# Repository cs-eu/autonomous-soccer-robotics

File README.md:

# Autonomous Soccer Robot

An autonomous, competition-ready soccer robot designed and built for a educational robotics competition.

---

## Overview

The **Autonomous Soccer Robot** was engineered to:

* Detect and track a ball using 360° vision
* Navigate the field holonomically in any direction
* Handle and shoot the ball autonomously
* Operate completely untethered under RoboCupJunior Soccer rules

Every part — from the **mechanical design** and **custom PCBs** to the **embedded firmware** and **computer vision** algorithms — was developed by our team.

This repository provides a complete, open-source reference for educational and research use.

---

## Project Structure

```
.
├── docs/                # Documentation and reference material
│   ├── electronics/     # Schematics, PCB layouts, and Eagle files
│   ├── hardware/        # CAD designs, drawings, and mechanical notes
│   └── parts-lists/     # Component, ordering, and assembly lists
│
├── firmware/            # Embedded control software (C/C++ / PlatformIO)
│   ├── calibration-tools/  # Sensor calibration and testing utilities
│   ├── main-controller/    # High-level control (movement, PID, logic)
│   ├── sensor-node/        # Sensor acquisition and preprocessing
│   └── tests/              # Unit and integration tests
│
├── libraries/           # Shared hardware abstraction and logic libraries
│   ├── Bodensensoren/   # Floor sensor modules
│   ├── IMU/             # IMU driver and orientation estimation
│   ├── TOF/             # Time-of-Flight distance sensing
│   ├── Motors/          # Motor control and PID regulation
│   ├── TACTICS/         # Robot state machine and strategy modules
│   └── ...              # Additional hardware interface libraries
│
├── mechanical/          # Physical design and fabrication files
│   ├── 3d-models/       # Fusion 360 models and 3D-print files (.stl, .f3d)
│   ├── eagle-pcb/       # Custom PCB layouts and Eagle libraries
│   └── metal-fabrication/ # CNC drawings, step files, and laser-cut designs
│
└── vision/              # Computer vision and image processing
    ├── docker/          # Dockerfiles for OpenCV build environments
    └── tinkerboard/     # Tinker Board vision software (Python + OpenCV)
```

---

## System Architecture

### Hardware Overview

* **Drive System:** Three-wheel omnidirectional base (holonomic drive)
* **Dribbler:** DC-motor-driven adhesive roller for ball handling
* **Kicker:** Solenoid-based shooting mechanism powered via capacitor buffer
* **Main Controller:** Dual **Teensy 3.6** microcontrollers for control & sensing
* **Vision Processor:** **ASUS Tinker Board** running OpenCV (Python)
* **Sensors:**

  * Raspberry Pi camera + parabolic mirror (360° vision)
  * 4× Time-of-Flight (ToF) distance sensors
  * 32× photoresistor array with RGB illumination for boundary detection

---

## Software Overview

| Layer             | Platform                     | Language                  | Description                                           |
| ----------------- | ---------------------------- | ------------------------- | ----------------------------------------------------- |
| **Vision**        | Tinker Board (SBC)           | Python + OpenCV           | Detects the ball and extracts angular bearing         |
| **Control**       | Teensy 3.6                   | C/C++ (Arduino Framework) | Motion control, PID regulation, actuator management   |
| **Communication** | Serial protocol (custom CRC) | C/Python                  | Reliable low-latency data exchange (<20 ms loop time) |

### Control Loop

The control system computes translational and rotational velocities from sensor inputs, applying:
[
u(t) = K_p e(t) + K_i \int e(t),dt + K_d \frac{de(t)}{dt}
]
Each wheel’s speed is regulated through independent PID loops for smooth, responsive motion.

---

## Mechanical Design

The chassis combines **CNC-milled aluminum** for structural integrity with **3D-printed polymer shells** for lightweight coverage and modular maintenance.
All components were modeled in **Autodesk Fusion 360**, allowing precise alignment and rapid iteration.

---

## Electronics

* **Custom PCBs** for motor drivers, solenoid control, and power regulation
* Designed using **Autodesk Eagle**
* Multiple voltage rails (12V / 5V / 3.3V) with overcurrent and thermal protection
* Modular connectors for fast servicing during competition

---

## Vision and Perception

The 360° vision system uses a **catadioptric setup** (camera + parabolic mirror) to obtain a full panoramic field view.
Processing steps include:

1. Image unwarping to cylindrical projection
2. Color filtering to detect the orange ball
3. Contour and centroid extraction
4. Angular position estimation relative to robot center

Additional data from ToF sensors and photoresistors provide:

* Boundary line detection
* Obstacle proximity sensing
* Position estimation support

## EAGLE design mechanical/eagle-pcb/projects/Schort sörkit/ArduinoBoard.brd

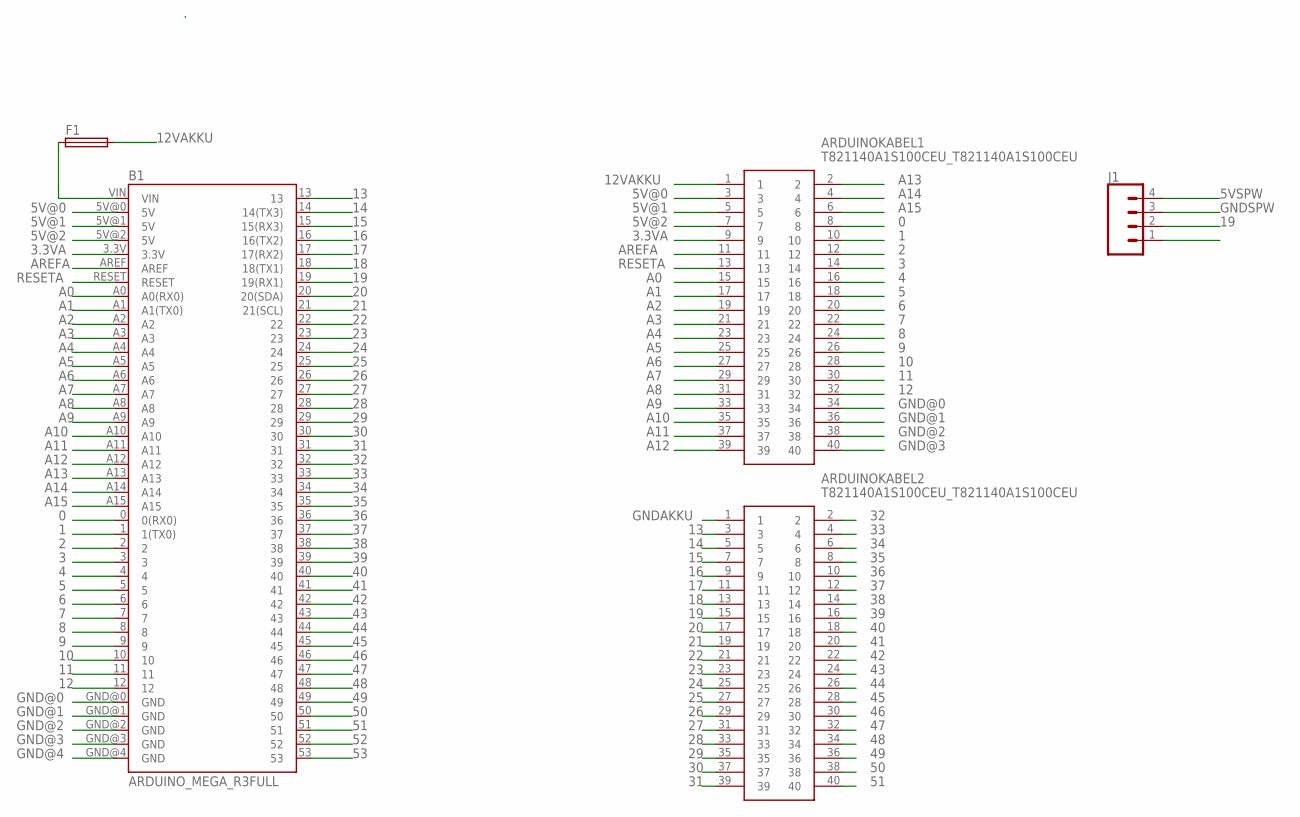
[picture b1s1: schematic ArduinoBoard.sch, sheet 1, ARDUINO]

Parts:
ARDUINOKABEL1, ARDUINOKABEL2: T821140A1S100CEU_T821140A1S100CEU; T821140A1S100CEU_SHDR40W64P254X254_2X20_5842X89
B1: ARDUINO_MEGA_R3FULL; ARDUINO_MEGA
F1: SH25
J1: CONN_04; 1X04

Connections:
0: ARDUINOKABEL1.8, B1.0 (0(RX0))
1: ARDUINOKABEL1.10, B1.1 (1(TX0))
2: ARDUINOKABEL1.12, B1.2; also elsewhere on the board
3: ARDUINOKABEL1.14, B1.3; also elsewhere on the board
3.3VA: ARDUINOKABEL1.9, B1.3.3V
4: ARDUINOKABEL1.16, B1.4; also elsewhere on the board
5: ARDUINOKABEL1.18, B1.5; also elsewhere on the board
5V@0: ARDUINOKABEL1.3, B1.5V@0 (5V); also elsewhere on the board
5V@1: ARDUINOKABEL1.5, B1.5V@1 (5V)
5V@2: ARDUINOKABEL1.7, B1.5V@2 (5V)
6: ARDUINOKABEL1.20, B1.6; also elsewhere on the board
7: ARDUINOKABEL1.22, B1.7
8: ARDUINOKABEL1.24, B1.8; also elsewhere on the board
9: ARDUINOKABEL1.26, B1.9
10: ARDUINOKABEL1.28, B1.10
11: ARDUINOKABEL1.30, B1.11
12: ARDUINOKABEL1.32, B1.12
12VAKKU: ARDUINOKABEL1.1, F1.2
13: ARDUINOKABEL2.3, B1.13
14: ARDUINOKABEL2.5, B1.14 (14(TX3))
15: ARDUINOKABEL2.7, B1.15 (15(RX3))
16: ARDUINOKABEL2.9, B1.16 (16(TX2))
17: ARDUINOKABEL2.11, B1.17 (17(RX2))
18: ARDUINOKABEL2.13, B1.18 (18(TX1)); also elsewhere on the board
19: ARDUINOKABEL2.15, B1.19 (19(RX1)), J1.2; also elsewhere on the board
20: ARDUINOKABEL2.17, B1.20 (20(SDA))
21: ARDUINOKABEL2.19, B1.21 (21(SCL))
22: ARDUINOKABEL2.21, B1.22
23: ARDUINOKABEL2.23, B1.23
24: ARDUINOKABEL2.25, B1.24
25: ARDUINOKABEL2.27, B1.25
26: ARDUINOKABEL2.29, B1.26
27: ARDUINOKABEL2.31, B1.27
28: ARDUINOKABEL2.33, B1.28
29: ARDUINOKABEL2.35, B1.29
30: ARDUINOKABEL2.37, B1.30
31: ARDUINOKABEL2.39, B1.31
32: ARDUINOKABEL2.2, B1.32
33: ARDUINOKABEL2.4, B1.33
34: ARDUINOKABEL2.6, B1.34
35: ARDUINOKABEL2.8, B1.35
36: ARDUINOKABEL2.10, B1.36
37: ARDUINOKABEL2.12, B1.37
38: ARDUINOKABEL2.14, B1.38
39: ARDUINOKABEL2.16, B1.39
40: ARDUINOKABEL2.18, B1.40
41: ARDUINOKABEL2.20, B1.41
42: ARDUINOKABEL2.22, B1.42
43: ARDUINOKABEL2.24, B1.43
44: ARDUINOKABEL2.26, B1.44
45: ARDUINOKABEL2.28, B1.45
46: ARDUINOKABEL2.30, B1.46
47: ARDUINOKABEL2.32, B1.47
48: ARDUINOKABEL2.34, B1.48
49: ARDUINOKABEL2.36, B1.49
50: ARDUINOKABEL2.38, B1.50
51: ARDUINOKABEL2.40, B1.51
52: B1.52
53: B1.53
A0: ARDUINOKABEL1.15, B1.A0 (A0(RX0))
A1: ARDUINOKABEL1.17, B1.A1 (A1(TX0))
A2: ARDUINOKABEL1.19, B1.A2
A3: ARDUINOKABEL1.21, B1.A3
A4: ARDUINOKABEL1.23, B1.A4
A5: ARDUINOKABEL1.25, B1.A5
A6: ARDUINOKABEL1.27, B1.A6
A7: ARDUINOKABEL1.29, B1.A7
A8: ARDUINOKABEL1.31, B1.A8
A9: ARDUINOKABEL1.33, B1.A9
A10: ARDUINOKABEL1.35, B1.A10
A11: ARDUINOKABEL1.37, B1.A11
A12: ARDUINOKABEL1.39, B1.A12
A13: ARDUINOKABEL1.2, B1.A13
A14: ARDUINOKABEL1.4, B1.A14
A15: ARDUINOKABEL1.6, B1.A15
AREFA: ARDUINOKABEL1.11, B1.AREF
GND@0: ARDUINOKABEL1.34, B1.GND@0 (GND); also elsewhere on the board
GND@1: ARDUINOKABEL1.36, B1.GND@1 (GND)
GND@2: ARDUINOKABEL1.38, B1.GND@2 (GND)
GND@3: ARDUINOKABEL1.40, B1.GND@3 (GND)
GND@4: B1.GND@4 (GND)
GNDAKKU: ARDUINOKABEL2.1
RESETA: ARDUINOKABEL1.13, B1.RESET
VIN: B1.VIN, F1.1

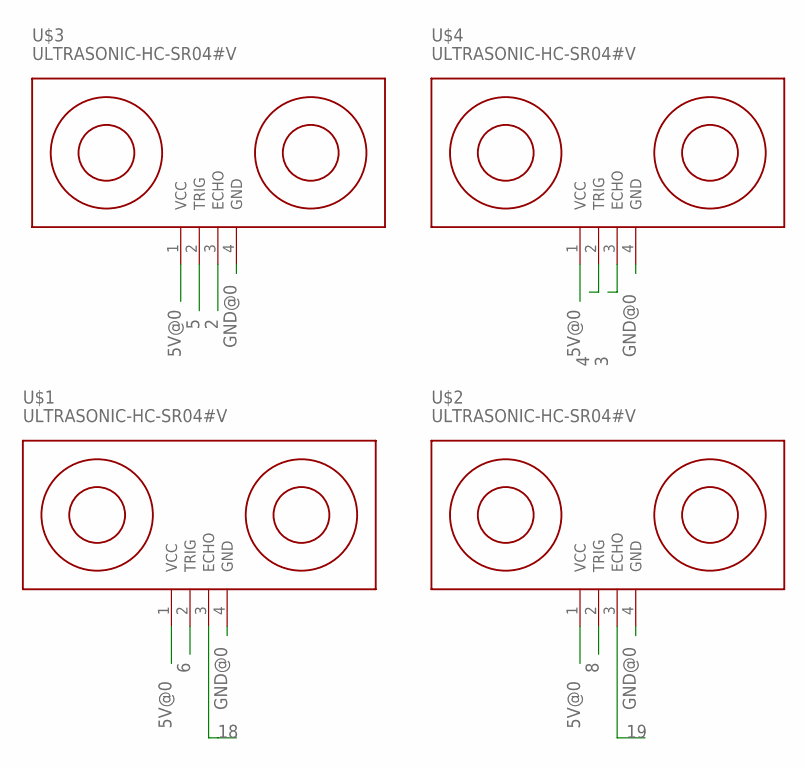
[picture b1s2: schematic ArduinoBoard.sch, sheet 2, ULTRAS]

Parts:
U$1, U$2, U$3, U$4: ULTRASONIC-HC-SR04#V

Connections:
2: U$3.3 (ECHO); also elsewhere on the board
3: U$4.3 (ECHO); also elsewhere on the board
4: U$4.2 (TRIG); also elsewhere on the board
5: U$3.2 (TRIG); also elsewhere on the board
5V@0: U$1.1 (VCC), U$2.1 (VCC), U$3.1 (VCC), U$4.1 (VCC); also elsewhere on the board
6: U$1.2 (TRIG); also elsewhere on the board
8: U$2.2 (TRIG); also elsewhere on the board
18: U$1.3 (ECHO); also elsewhere on the board
19: U$2.3 (ECHO); also elsewhere on the board
GND@0: U$1.4 (GND), U$2.4 (GND), U$3.4 (GND), U$4.4 (GND); also elsewhere on the board

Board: 2 copper layers, 9 parts (0 on the bottom side), 80 nets, no tracks yet.

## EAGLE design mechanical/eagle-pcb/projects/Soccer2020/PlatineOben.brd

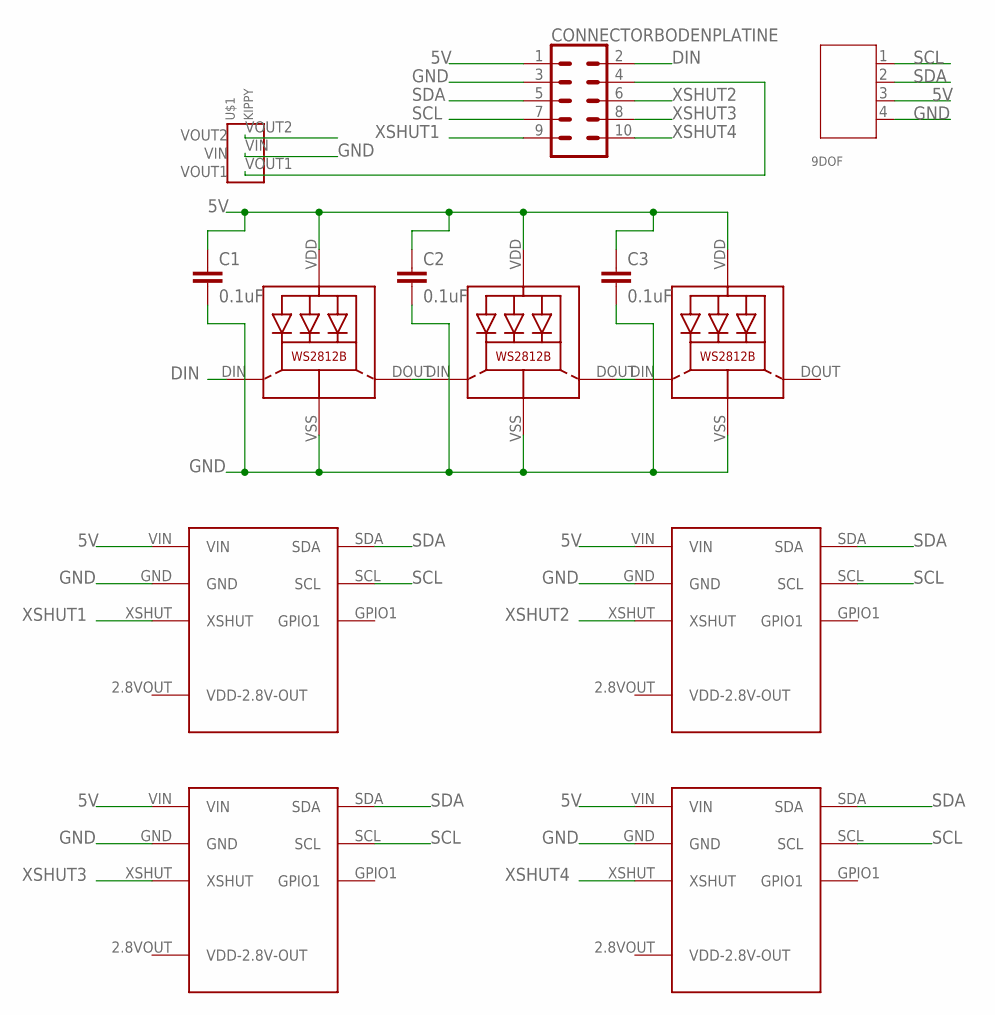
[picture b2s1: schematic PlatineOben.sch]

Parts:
9DOF: 4P-2.0; JST-PH4
C1, C2, C3: 0.1uF; C0805
CONNECTORBODENPLATINE: CONN_05X2; 2X5-SHROUDED(3D)
LED1, LED2, LED3: WS2812B
TOFH: TOFPOLOLUSTEHEND; TOFPOLOLU_STEHEND
TOFL: TOFPOLOLUSTEHEND; TOFPOLOLU_STEHEND
TOFR: TOFPOLOLUSTEHEND; TOFPOLOLU_STEHEND
TOFV: TOFPOLOLUSTEHEND; TOFPOLOLU_STEHEND
U$1: KIPPY

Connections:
5V: 9DOF.3, C1.1, C2.1, C3.1, CONNECTORBODENPLATINE.1, LED1.VDD, LED2.VDD, LED3.VDD, TOFH.VIN, TOFL.VIN, TOFR.VIN, TOFV.VIN
DIN: CONNECTORBODENPLATINE.2, LED1.DIN (DI)
GND: 9DOF.4, C1.2, C2.2, C3.2, CONNECTORBODENPLATINE.3, LED1.VSS (GND), LED2.VSS (GND), LED3.VSS (GND), TOFH.GND, TOFL.GND, TOFR.GND, TOFV.GND, U$1.VIN
unnamed: CONNECTORBODENPLATINE.4, U$1.VOUT1
unnamed: LED1.DOUT (DO), LED2.DIN (DI)
unnamed: LED2.DOUT (DO), LED3.DIN (DI)
SCL: 9DOF.1, CONNECTORBODENPLATINE.7, TOFH.SCL, TOFL.SCL, TOFR.SCL, TOFV.SCL
SDA: 9DOF.2, CONNECTORBODENPLATINE.5, TOFH.SDA, TOFL.SDA, TOFR.SDA, TOFV.SDA
XSHUT1: CONNECTORBODENPLATINE.9, TOFR.XSHUT
XSHUT2: CONNECTORBODENPLATINE.6, TOFL.XSHUT
XSHUT3: CONNECTORBODENPLATINE.8, TOFV.XSHUT
XSHUT4: CONNECTORBODENPLATINE.10, TOFH.XSHUT

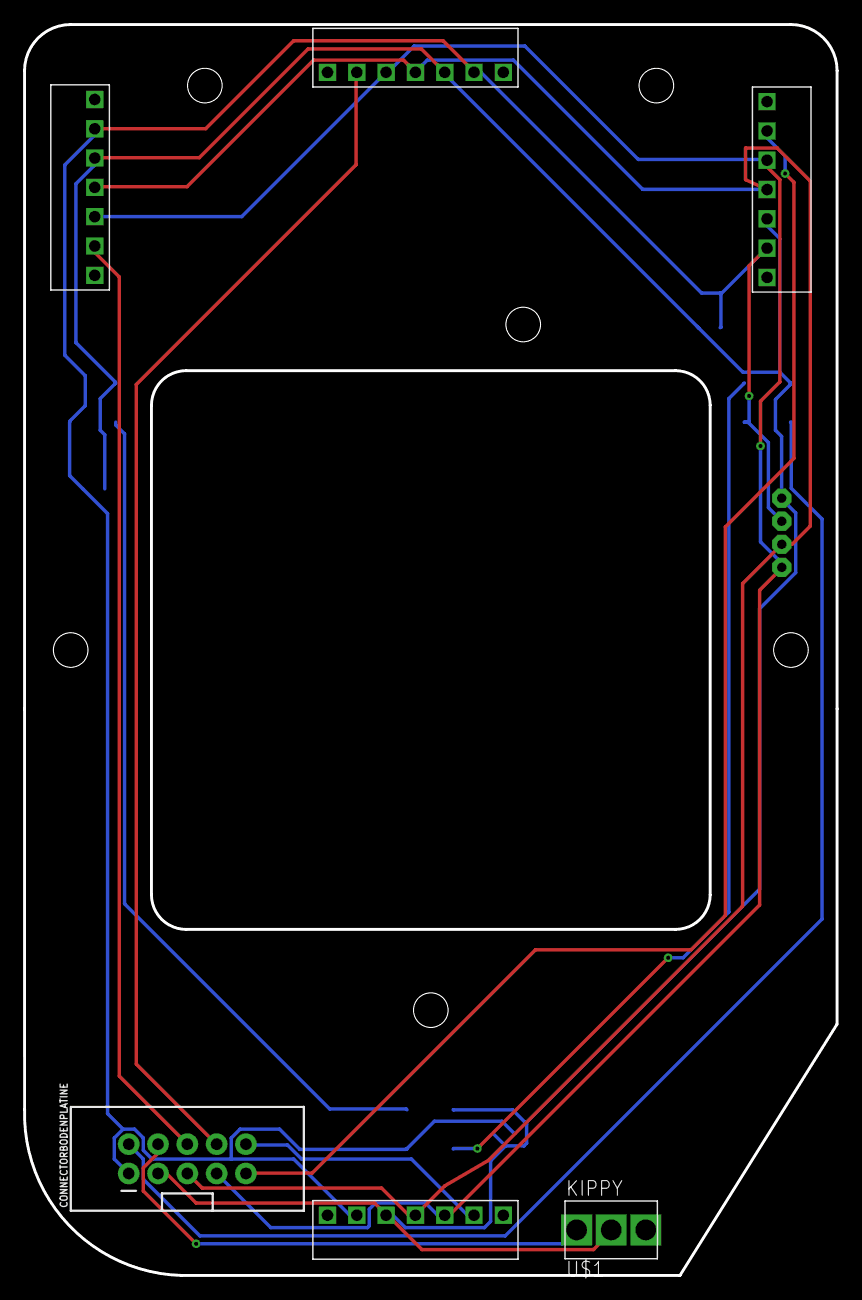
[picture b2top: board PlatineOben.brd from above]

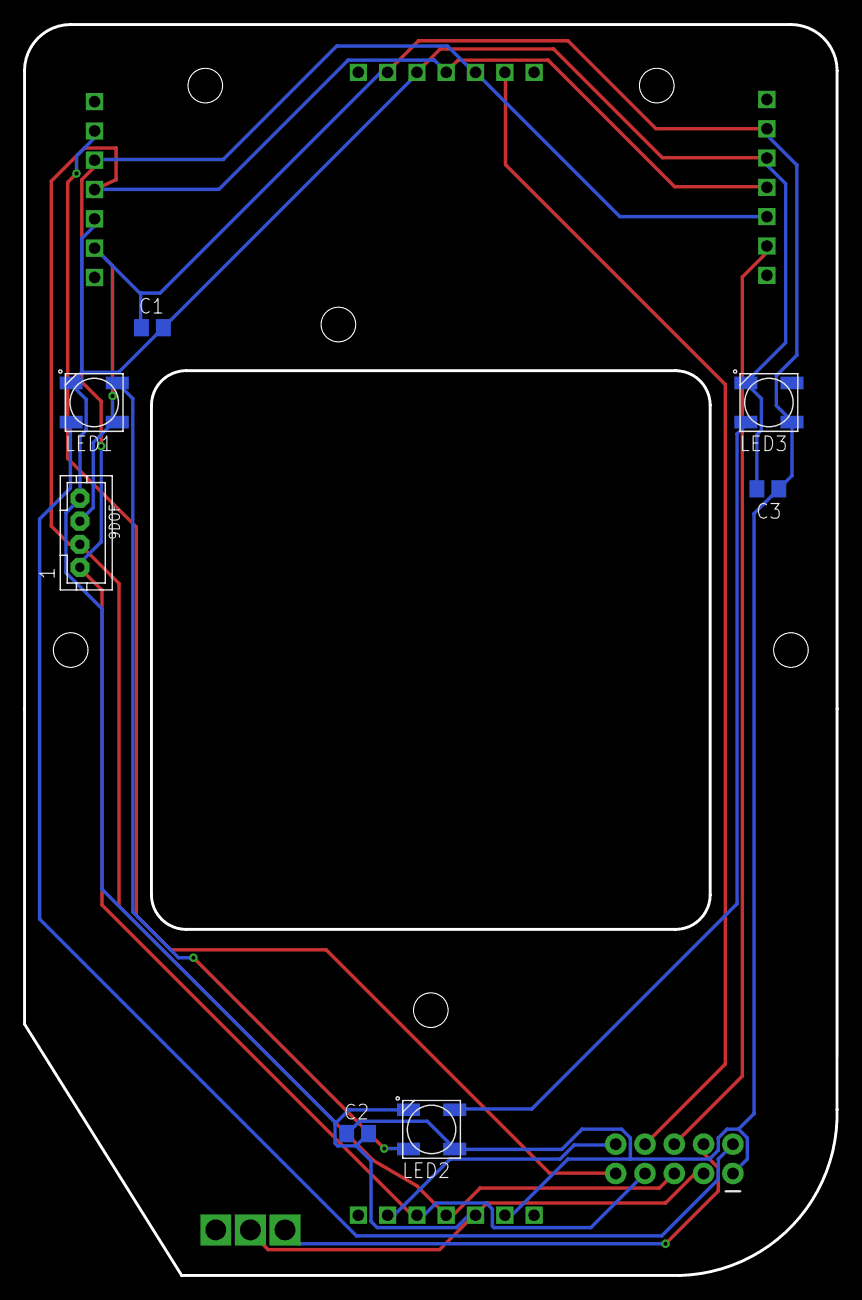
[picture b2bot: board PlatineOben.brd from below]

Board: 2 copper layers, 70.4 x 108.4 mm, 13 parts (7 on the bottom side), 12 nets.

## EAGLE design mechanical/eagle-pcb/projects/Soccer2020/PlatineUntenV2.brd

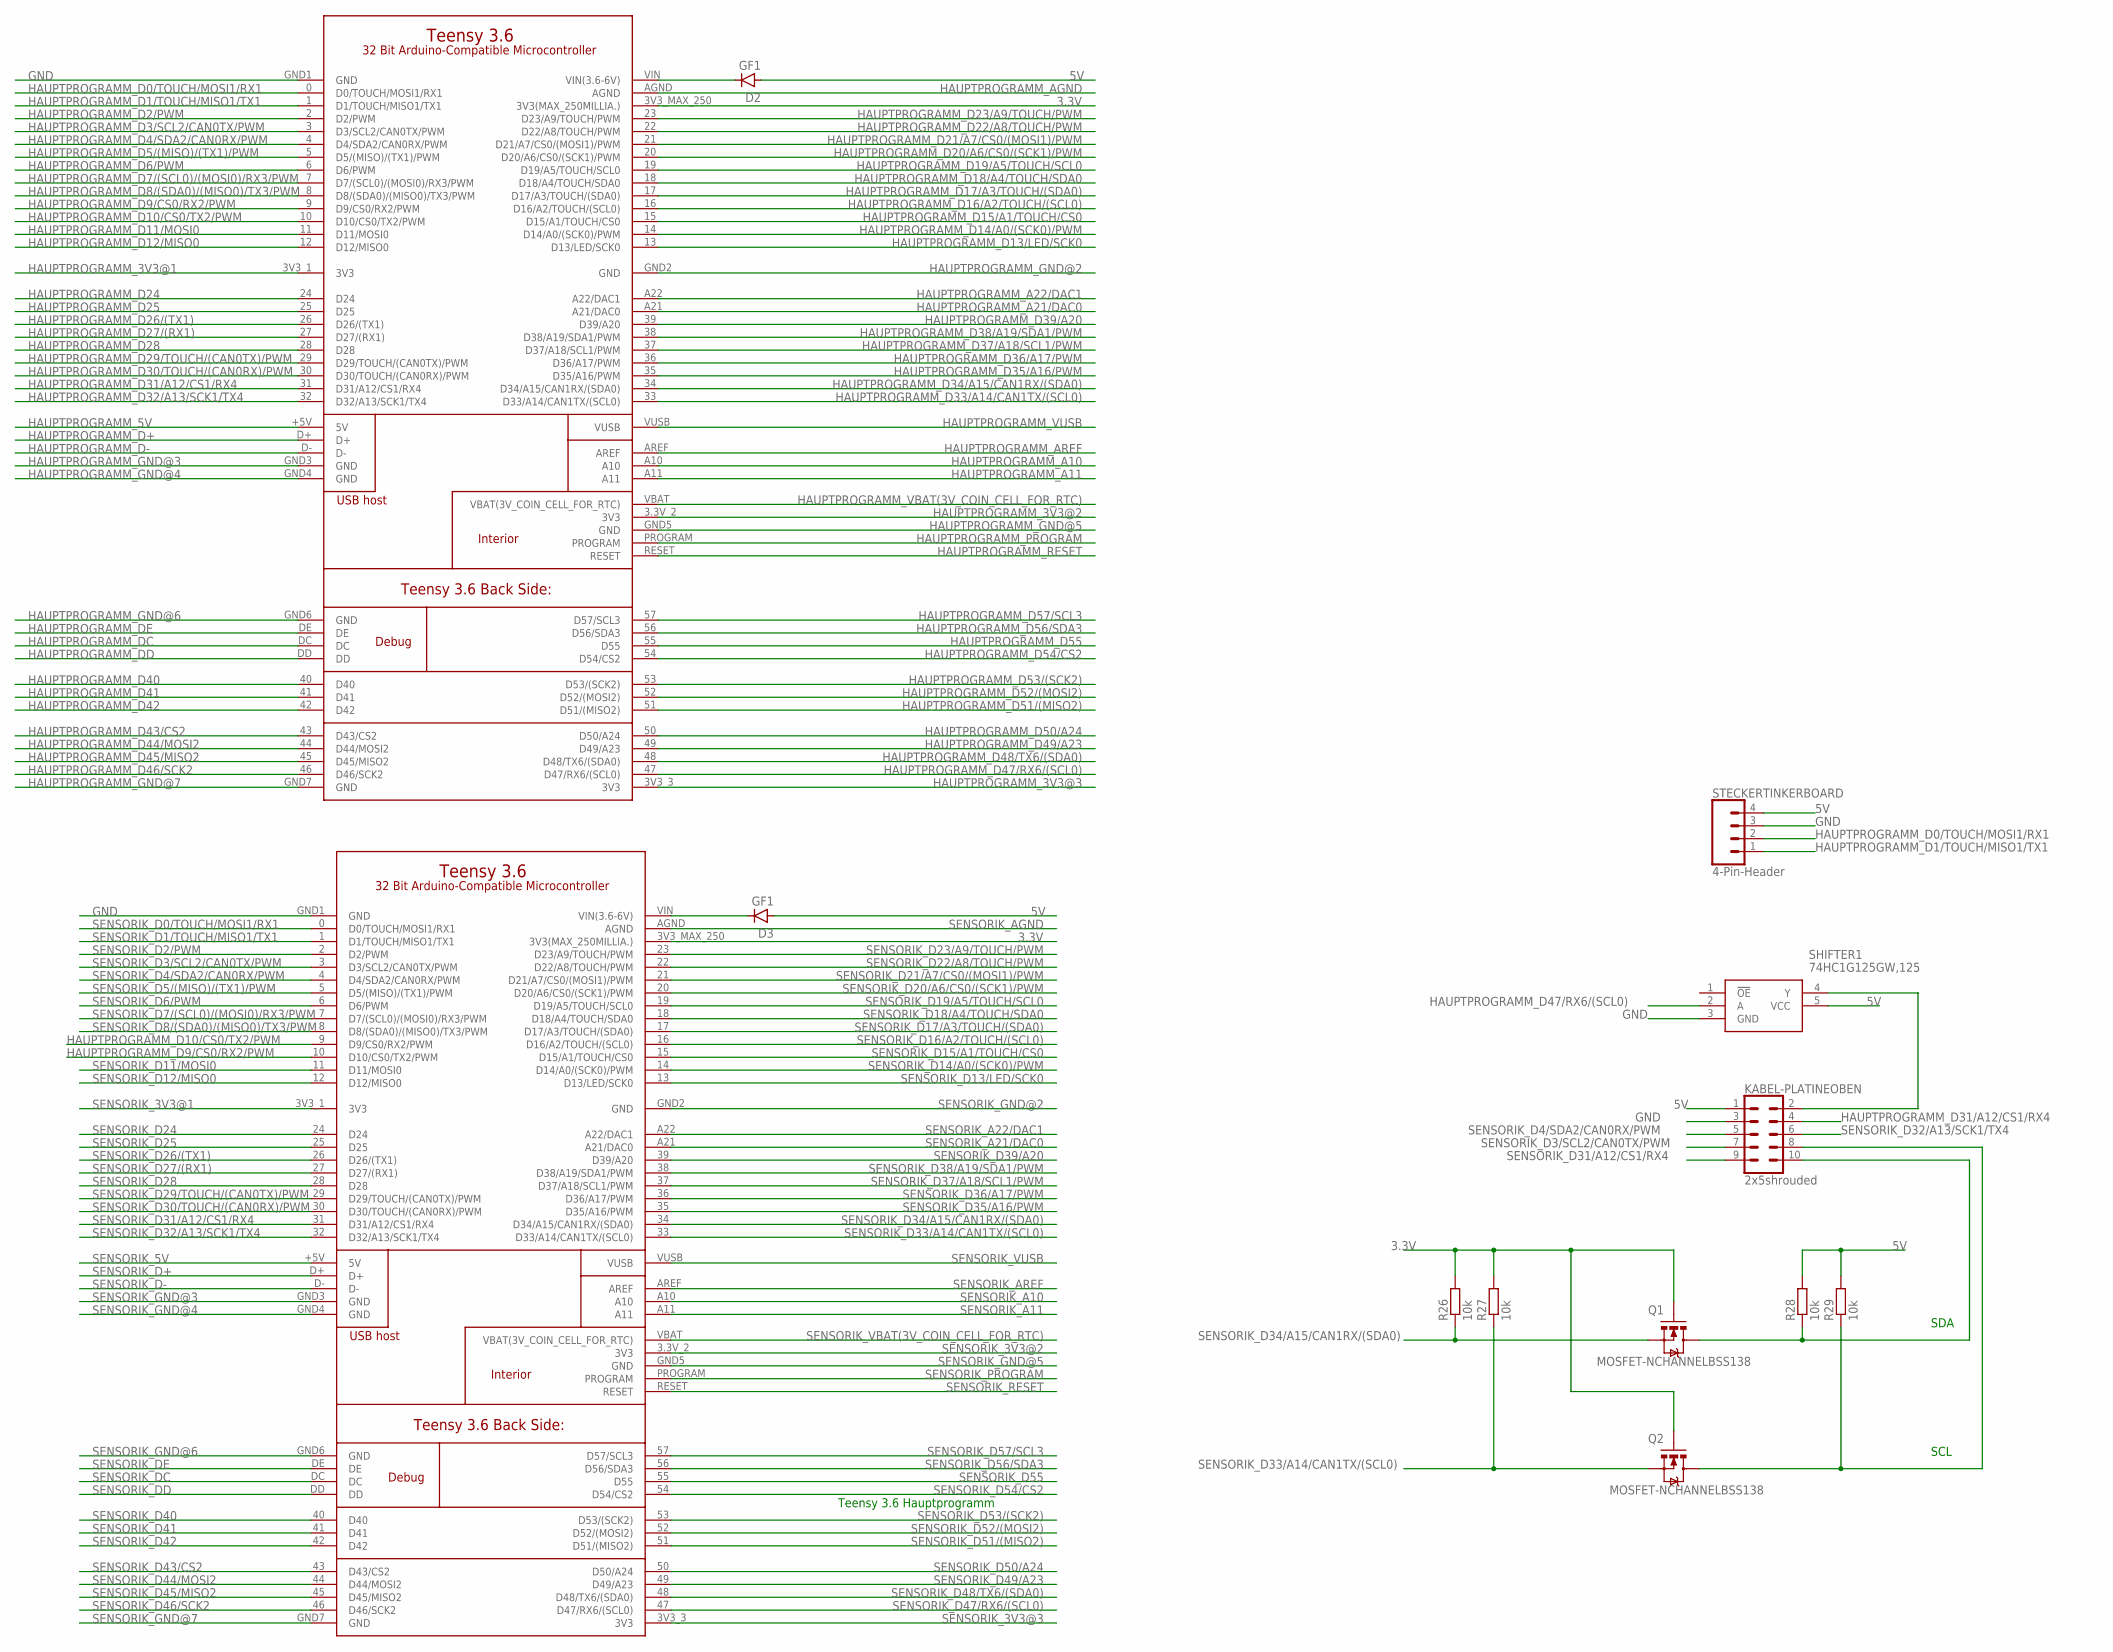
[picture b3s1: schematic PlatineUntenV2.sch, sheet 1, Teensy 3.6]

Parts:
D2, D3: GF1; SMA-DO214AC
HAUPTPROGRAMM: TEENSY3.6_FULL
KABEL-PLATINEOBEN: 2x5shrouded; 2X5-SHROUDED(3D)
Q1, Q2: MOSFET-NCHANNELBSS138; SOT23
R26, R27, R28, R29: 10k; R0805
SENSORIK: TEENSY3.6_FULL
SHIFTER1: 74HC1G125GW,125; SOT65P212X110-5N
STECKERTINKERBOARD: 4-Pin-Header; 1X04

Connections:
3.3V: HAUPTPROGRAMM.3V3_MAX_250 (3V3(MAX_250MILLIA.)), Q1.1 (G), Q2.1 (G), R26.2, R27.2, SENSORIK.3V3_MAX_250 (3V3(MAX_250MILLIA.)); also elsewhere on the board
5V: D2.A, D3.A, KABEL-PLATINEOBEN.1, R28.2, R29.2, SHIFTER1.5 (VCC), STECKERTINKERBOARD.4; also elsewhere on the board
GND: HAUPTPROGRAMM.GND1 (GND), KABEL-PLATINEOBEN.3, SENSORIK.GND1 (GND), SHIFTER1.3 (GND), STECKERTINKERBOARD.3; also elsewhere on the board
HAUPTPROGRAMM_3V3@1: HAUPTPROGRAMM.3V3_1 (3V3)
HAUPTPROGRAMM_3V3@2: HAUPTPROGRAMM.3.3V_2 (3V3)
HAUPTPROGRAMM_3V3@3: HAUPTPROGRAMM.3V3_3 (3V3)
HAUPTPROGRAMM_5V: HAUPTPROGRAMM.+5V (5V)
HAUPTPROGRAMM_A10: HAUPTPROGRAMM.A10
HAUPTPROGRAMM_A11: HAUPTPROGRAMM.A11
HAUPTPROGRAMM_A21/DAC0: HAUPTPROGRAMM.A21 (A21/DAC0)
HAUPTPROGRAMM_A22/DAC1: HAUPTPROGRAMM.A22 (A22/DAC1)
HAUPTPROGRAMM_AGND: HAUPTPROGRAMM.AGND
HAUPTPROGRAMM_AREF: HAUPTPROGRAMM.AREF
HAUPTPROGRAMM_D0/TOUCH/MOSI1/RX1: HAUPTPROGRAMM.0 (D0/TOUCH/MOSI1/RX1), STECKERTINKERBOARD.2
HAUPTPROGRAMM_D1/TOUCH/MISO1/TX1: HAUPTPROGRAMM.1 (D1/TOUCH/MISO1/TX1), STECKERTINKERBOARD.1
HAUPTPROGRAMM_D2/PWM: HAUPTPROGRAMM.2 (D2/PWM); also elsewhere on the board
HAUPTPROGRAMM_D3/SCL2/CAN0TX/PWM: HAUPTPROGRAMM.3 (D3/SCL2/CAN0TX/PWM)
HAUPTPROGRAMM_D4/SDA2/CAN0RX/PWM: HAUPTPROGRAMM.4 (D4/SDA2/CAN0RX/PWM); also elsewhere on the board
HAUPTPROGRAMM_D5/(MISO)/(TX1)/PWM: HAUPTPROGRAMM.5 (D5/(MISO)/(TX1)/PWM)
HAUPTPROGRAMM_D6/PWM: HAUPTPROGRAMM.6 (D6/PWM); also elsewhere on the board
HAUPTPROGRAMM_D7/(SCL0)/(MOSI0)/RX3/PWM: HAUPTPROGRAMM.7 (D7/(SCL0)/(MOSI0)/RX3/PWM); also elsewhere on the board
HAUPTPROGRAMM_D8/(SDA0)/(MISO0)/TX3/PWM: HAUPTPROGRAMM.8 (D8/(SDA0)/(MISO0)/TX3/PWM)
HAUPTPROGRAMM_D9/CS0/RX2/PWM: HAUPTPROGRAMM.9 (D9/CS0/RX2/PWM), SENSORIK.10 (D10/CS0/TX2/PWM)
HAUPTPROGRAMM_D10/CS0/TX2/PWM: HAUPTPROGRAMM.10 (D10/CS0/TX2/PWM), SENSORIK.9 (D9/CS0/RX2/PWM)
HAUPTPROGRAMM_D11/MOSI0: HAUPTPROGRAMM.11 (D11/MOSI0); also elsewhere on the board
HAUPTPROGRAMM_D12/MISO0: HAUPTPROGRAMM.12 (D12/MISO0)
HAUPTPROGRAMM_D13/LED/SCK0: HAUPTPROGRAMM.13 (D13/LED/SCK0); also elsewhere on the board
HAUPTPROGRAMM_D14/A0/(SCK0)/PWM: HAUPTPROGRAMM.14 (D14/A0/(SCK0)/PWM); also elsewhere on the board
HAUPTPROGRAMM_D15/A1/TOUCH/CS0: HAUPTPROGRAMM.15 (D15/A1/TOUCH/CS0); also elsewhere on the board
HAUPTPROGRAMM_D16/A2/TOUCH/(SCL0): HAUPTPROGRAMM.16 (D16/A2/TOUCH/(SCL0)); also elsewhere on the board
HAUPTPROGRAMM_D17/A3/TOUCH/(SDA0): HAUPTPROGRAMM.17 (D17/A3/TOUCH/(SDA0)); also elsewhere on the board
HAUPTPROGRAMM_D18/A4/TOUCH/SDA0: HAUPTPROGRAMM.18 (D18/A4/TOUCH/SDA0); also elsewhere on the board
HAUPTPROGRAMM_D19/A5/TOUCH/SCL0: HAUPTPROGRAMM.19 (D19/A5/TOUCH/SCL0); also elsewhere on the board
HAUPTPROGRAMM_D20/A6/CS0/(SCK1)/PWM: HAUPTPROGRAMM.20 (D20/A6/CS0/(SCK1)/PWM); also elsewhere on the board
HAUPTPROGRAMM_D21/A7/CS0/(MOSI1)/PWM: HAUPTPROGRAMM.21 (D21/A7/CS0/(MOSI1)/PWM); also elsewhere on the board
HAUPTPROGRAMM_D22/A8/TOUCH/PWM: HAUPTPROGRAMM.22 (D22/A8/TOUCH/PWM); also elsewhere on the board
HAUPTPROGRAMM_D23/A9/TOUCH/PWM: HAUPTPROGRAMM.23 (D23/A9/TOUCH/PWM); also elsewhere on the board
HAUPTPROGRAMM_D24: HAUPTPROGRAMM.24 (D24); also elsewhere on the board
HAUPTPROGRAMM_D25: HAUPTPROGRAMM.25 (D25); also elsewhere on the board
HAUPTPROGRAMM_D26/(TX1): HAUPTPROGRAMM.26 (D26/(TX1)); also elsewhere on the board
HAUPTPROGRAMM_D27/(RX1): HAUPTPROGRAMM.27 (D27/(RX1))
HAUPTPROGRAMM_D28: HAUPTPROGRAMM.28 (D28); also elsewhere on the board
HAUPTPROGRAMM_D29/TOUCH/(CAN0TX)/PWM: HAUPTPROGRAMM.29 (D29/TOUCH/(CAN0TX)/PWM); also elsewhere on the board
HAUPTPROGRAMM_D30/TOUCH/(CAN0RX)/PWM: HAUPTPROGRAMM.30 (D30/TOUCH/(CAN0RX)/PWM)
HAUPTPROGRAMM_D31/A12/CS1/RX4: HAUPTPROGRAMM.31 (D31/A12/CS1/RX4), KABEL-PLATINEOBEN.4
HAUPTPROGRAMM_D32/A13/SCK1/TX4: HAUPTPROGRAMM.32 (D32/A13/SCK1/TX4); also elsewhere on the board
HAUPTPROGRAMM_D33/A14/CAN1TX/(SCL0): HAUPTPROGRAMM.33 (D33/A14/CAN1TX/(SCL0)); also elsewhere on the board
HAUPTPROGRAMM_D34/A15/CAN1RX/(SDA0): HAUPTPROGRAMM.34 (D34/A15/CAN1RX/(SDA0)); also elsewhere on the board
HAUPTPROGRAMM_D35/A16/PWM: HAUPTPROGRAMM.35 (D35/A16/PWM); also elsewhere on the board
HAUPTPROGRAMM_D36/A17/PWM: HAUPTPROGRAMM.36 (D36/A17/PWM); also elsewhere on the board
HAUPTPROGRAMM_D37/A18/SCL1/PWM: HAUPTPROGRAMM.37 (D37/A18/SCL1/PWM); also elsewhere on the board
HAUPTPROGRAMM_D38/A19/SDA1/PWM: HAUPTPROGRAMM.38 (D38/A19/SDA1/PWM); also elsewhere on the board
HAUPTPROGRAMM_D39/A20: HAUPTPROGRAMM.39 (D39/A20); also elsewhere on the board
HAUPTPROGRAMM_D40: HAUPTPROGRAMM.40 (D40); also elsewhere on the board
HAUPTPROGRAMM_D41: HAUPTPROGRAMM.41 (D41); also elsewhere on the board
HAUPTPROGRAMM_D42: HAUPTPROGRAMM.42 (D42); also elsewhere on the board
HAUPTPROGRAMM_D43/CS2: HAUPTPROGRAMM.43 (D43/CS2); also elsewhere on the board
HAUPTPROGRAMM_D44/MOSI2: HAUPTPROGRAMM.44 (D44/MOSI2); also elsewhere on the board
HAUPTPROGRAMM_D45/MISO2: HAUPTPROGRAMM.45 (D45/MISO2); also elsewhere on the board
HAUPTPROGRAMM_D46/SCK2: HAUPTPROGRAMM.46 (D46/SCK2); also elsewhere on the board
HAUPTPROGRAMM_D47/RX6/(SCL0): HAUPTPROGRAMM.47 (D47/RX6/(SCL0)), SHIFTER1.2 (A)
HAUPTPROGRAMM_D48/TX6/(SDA0): HAUPTPROGRAMM.48 (D48/TX6/(SDA0)); also elsewhere on the board
HAUPTPROGRAMM_D49/A23: HAUPTPROGRAMM.49 (D49/A23); also elsewhere on the board
HAUPTPROGRAMM_D50/A24: HAUPTPROGRAMM.50 (D50/A24)
HAUPTPROGRAMM_D51/(MISO2): HAUPTPROGRAMM.51 (D51/(MISO2)); also elsewhere on the board
HAUPTPROGRAMM_D52/(MOSI2): HAUPTPROGRAMM.52 (D52/(MOSI2))
HAUPTPROGRAMM_D53/(SCK2): HAUPTPROGRAMM.53 (D53/(SCK2)); also elsewhere on the board
HAUPTPROGRAMM_D54/CS2: HAUPTPROGRAMM.54 (D54/CS2); also elsewhere on the board
HAUPTPROGRAMM_D55: HAUPTPROGRAMM.55 (D55); also elsewhere on the board
HAUPTPROGRAMM_D56/SDA3: HAUPTPROGRAMM.56 (D56/SDA3)
HAUPTPROGRAMM_D57/SCL3: HAUPTPROGRAMM.57 (D57/SCL3)
HAUPTPROGRAMM_D+: HAUPTPROGRAMM.D+
HAUPTPROGRAMM_D-: HAUPTPROGRAMM.D-
HAUPTPROGRAMM_DC: HAUPTPROGRAMM.DC
HAUPTPROGRAMM_DD: HAUPTPROGRAMM.DD
HAUPTPROGRAMM_DE: HAUPTPROGRAMM.DE
HAUPTPROGRAMM_GND@2: HAUPTPROGRAMM.GND2 (GND)
HAUPTPROGRAMM_GND@3: HAUPTPROGRAMM.GND3 (GND)
HAUPTPROGRAMM_GND@4: HAUPTPROGRAMM.GND4 (GND)
HAUPTPROGRAMM_GND@5: HAUPTPROGRAMM.GND5 (GND)
HAUPTPROGRAMM_GND@6: HAUPTPROGRAMM.GND6 (GND)
HAUPTPROGRAMM_GND@7: HAUPTPROGRAMM.GND7 (GND)
HAUPTPROGRAMM_PROGRAM: HAUPTPROGRAMM.PROGRAM
HAUPTPROGRAMM_RESET: HAUPTPROGRAMM.RESET
HAUPTPROGRAMM_VBAT(3V_COIN_CELL_FOR_RTC): HAUPTPROGRAMM.VBAT (VBAT(3V_COIN_CELL_FOR_RTC))
HAUPTPROGRAMM_VUSB: HAUPTPROGRAMM.VUSB
unnamed: D2.K (C), HAUPTPROGRAMM.VIN (VIN(3.6-6V))
unnamed: D3.K (C), SENSORIK.VIN (VIN(3.6-6V))
unnamed: KABEL-PLATINEOBEN.10, Q1.3 (D), R28.1
unnamed: KABEL-PLATINEOBEN.8, Q2.3 (D), R29.1
unnamed: KABEL-PLATINEOBEN.2, SHIFTER1.4 (Y)
SENSORIK_3V3@1: SENSORIK.3V3_1 (3V3)
SENSORIK_3V3@2: SENSORIK.3.3V_2 (3V3)
SENSORIK_3V3@3: SENSORIK.3V3_3 (3V3)
SENSORIK_5V: SENSORIK.+5V (5V)
SENSORIK_A10: SENSORIK.A10
SENSORIK_A11: SENSORIK.A11
SENSORIK_A21/DAC0: SENSORIK.A21 (A21/DAC0)
SENSORIK_A22/DAC1: SENSORIK.A22 (A22/DAC1)
SENSORIK_AGND: SENSORIK.AGND
SENSORIK_AREF: SENSORIK.AREF
SENSORIK_D0/TOUCH/MOSI1/RX1: SENSORIK.0 (D0/TOUCH/MOSI1/RX1)
SENSORIK_D1/TOUCH/MISO1/TX1: SENSORIK.1 (D1/TOUCH/MISO1/TX1)
SENSORIK_D2/PWM: SENSORIK.2 (D2/PWM)
SENSORIK_D3/SCL2/CAN0TX/PWM: KABEL-PLATINEOBEN.7, SENSORIK.3 (D3/SCL2/CAN0TX/PWM); also elsewhere on the board
SENSORIK_D4/SDA2/CAN0RX/PWM: KABEL-PLATINEOBEN.5, SENSORIK.4 (D4/SDA2/CAN0RX/PWM); also elsewhere on the board
SENSORIK_D5/(MISO)/(TX1)/PWM: SENSORIK.5 (D5/(MISO)/(TX1)/PWM)
SENSORIK_D6/PWM: SENSORIK.6 (D6/PWM)
SENSORIK_D7/(SCL0)/(MOSI0)/RX3/PWM: SENSORIK.7 (D7/(SCL0)/(MOSI0)/RX3/PWM)
SENSORIK_D8/(SDA0)/(MISO0)/TX3/PWM: SENSORIK.8 (D8/(SDA0)/(MISO0)/TX3/PWM)
SENSORIK_D11/MOSI0: SENSORIK.11 (D11/MOSI0)
SENSORIK_D12/MISO0: SENSORIK.12 (D12/MISO0)
SENSORIK_D13/LED/SCK0: SENSORIK.13 (D13/LED/SCK0)
SENSORIK_D14/A0/(SCK0)/PWM: SENSORIK.14 (D14/A0/(SCK0)/PWM)
SENSORIK_D15/A1/TOUCH/CS0: SENSORIK.15 (D15/A1/TOUCH/CS0)
SENSORIK_D16/A2/TOUCH/(SCL0): SENSORIK.16 (D16/A2/TOUCH/(SCL0))
SENSORIK_D17/A3/TOUCH/(SDA0): SENSORIK.17 (D17/A3/TOUCH/(SDA0))
SENSORIK_D18/A4/TOUCH/SDA0: SENSORIK.18 (D18/A4/TOUCH/SDA0); also elsewhere on the board
SENSORIK_D19/A5/TOUCH/SCL0: SENSORIK.19 (D19/A5/TOUCH/SCL0); also elsewhere on the board
SENSORIK_D20/A6/CS0/(SCK1)/PWM: SENSORIK.20 (D20/A6/CS0/(SCK1)/PWM)
SENSORIK_D21/A7/CS0/(MOSI1)/PWM: SENSORIK.21 (D21/A7/CS0/(MOSI1)/PWM)
SENSORIK_D22/A8/TOUCH/PWM: SENSORIK.22 (D22/A8/TOUCH/PWM)
SENSORIK_D23/A9/TOUCH/PWM: SENSORIK.23 (D23/A9/TOUCH/PWM)
SENSORIK_D24: SENSORIK.24 (D24); also elsewhere on the board
SENSORIK_D25: SENSORIK.25 (D25); also elsewhere on the board
SENSORIK_D26/(TX1): SENSORIK.26 (D26/(TX1))
SENSORIK_D27/(RX1): SENSORIK.27 (D27/(RX1))
SENSORIK_D28: SENSORIK.28 (D28); also elsewhere on the board
SENSORIK_D29/TOUCH/(CAN0TX)/PWM: SENSORIK.29 (D29/TOUCH/(CAN0TX)/PWM)
SENSORIK_D30/TOUCH/(CAN0RX)/PWM: SENSORIK.30 (D30/TOUCH/(CAN0RX)/PWM)
SENSORIK_D31/A12/CS1/RX4: KABEL-PLATINEOBEN.9, SENSORIK.31 (D31/A12/CS1/RX4)
SENSORIK_D32/A13/SCK1/TX4: KABEL-PLATINEOBEN.6, SENSORIK.32 (D32/A13/SCK1/TX4)
SENSORIK_D33/A14/CAN1TX/(SCL0): Q2.2 (S), R27.1, SENSORIK.33 (D33/A14/CAN1TX/(SCL0))
SENSORIK_D34/A15/CAN1RX/(SDA0): Q1.2 (S), R26.1, SENSORIK.34 (D34/A15/CAN1RX/(SDA0))
SENSORIK_D35/A16/PWM: SENSORIK.35 (D35/A16/PWM)
SENSORIK_D36/A17/PWM: SENSORIK.36 (D36/A17/PWM)
SENSORIK_D37/A18/SCL1/PWM: SENSORIK.37 (D37/A18/SCL1/PWM); also elsewhere on the board
SENSORIK_D38/A19/SDA1/PWM: SENSORIK.38 (D38/A19/SDA1/PWM); also elsewhere on the board
SENSORIK_D39/A20: SENSORIK.39 (D39/A20)
SENSORIK_D40: SENSORIK.40 (D40); also elsewhere on the board
SENSORIK_D41: SENSORIK.41 (D41); also elsewhere on the board
SENSORIK_D42: SENSORIK.42 (D42); also elsewhere on the board
SENSORIK_D43/CS2: SENSORIK.43 (D43/CS2); also elsewhere on the board
SENSORIK_D44/MOSI2: SENSORIK.44 (D44/MOSI2)
SENSORIK_D45/MISO2: SENSORIK.45 (D45/MISO2)
SENSORIK_D46/SCK2: SENSORIK.46 (D46/SCK2); also elsewhere on the board
SENSORIK_D47/RX6/(SCL0): SENSORIK.47 (D47/RX6/(SCL0))
SENSORIK_D48/TX6/(SDA0): SENSORIK.48 (D48/TX6/(SDA0))
SENSORIK_D49/A23: SENSORIK.49 (D49/A23)
SENSORIK_D50/A24: SENSORIK.50 (D50/A24)
SENSORIK_D51/(MISO2): SENSORIK.51 (D51/(MISO2))
SENSORIK_D52/(MOSI2): SENSORIK.52 (D52/(MOSI2))
SENSORIK_D53/(SCK2): SENSORIK.53 (D53/(SCK2))
SENSORIK_D54/CS2: SENSORIK.54 (D54/CS2)
SENSORIK_D55: SENSORIK.55 (D55)
SENSORIK_D56/SDA3: SENSORIK.56 (D56/SDA3); also elsewhere on the board
SENSORIK_D57/SCL3: SENSORIK.57 (D57/SCL3); also elsewhere on the board
SENSORIK_D+: SENSORIK.D+
SENSORIK_D-: SENSORIK.D-
SENSORIK_DC: SENSORIK.DC
SENSORIK_DD: SENSORIK.DD
SENSORIK_DE: SENSORIK.DE
SENSORIK_GND@2: SENSORIK.GND2 (GND)
SENSORIK_GND@3: SENSORIK.GND3 (GND)
SENSORIK_GND@4: SENSORIK.GND4 (GND)
SENSORIK_GND@5: SENSORIK.GND5 (GND)
SENSORIK_GND@6: SENSORIK.GND6 (GND)
SENSORIK_GND@7: SENSORIK.GND7 (GND)
SENSORIK_PROGRAM: SENSORIK.PROGRAM
SENSORIK_RESET: SENSORIK.RESET
SENSORIK_VBAT(3V_COIN_CELL_FOR_RTC): SENSORIK.VBAT (VBAT(3V_COIN_CELL_FOR_RTC))
SENSORIK_VUSB: SENSORIK.VUSB

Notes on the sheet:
Teensy 3.6 Hauptprogramm
SDA
SCL

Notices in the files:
parts and their libraries:
SparkFun-Boards: Licensing: Creative Commons ShareAlike 4.0 International - https://creativecommons.org/licenses/by-sa/4.0
diy-modules: Released under the Creative Commons Attribution 4.0 International License: http://creativecommons.org/licenses/by/4.0
